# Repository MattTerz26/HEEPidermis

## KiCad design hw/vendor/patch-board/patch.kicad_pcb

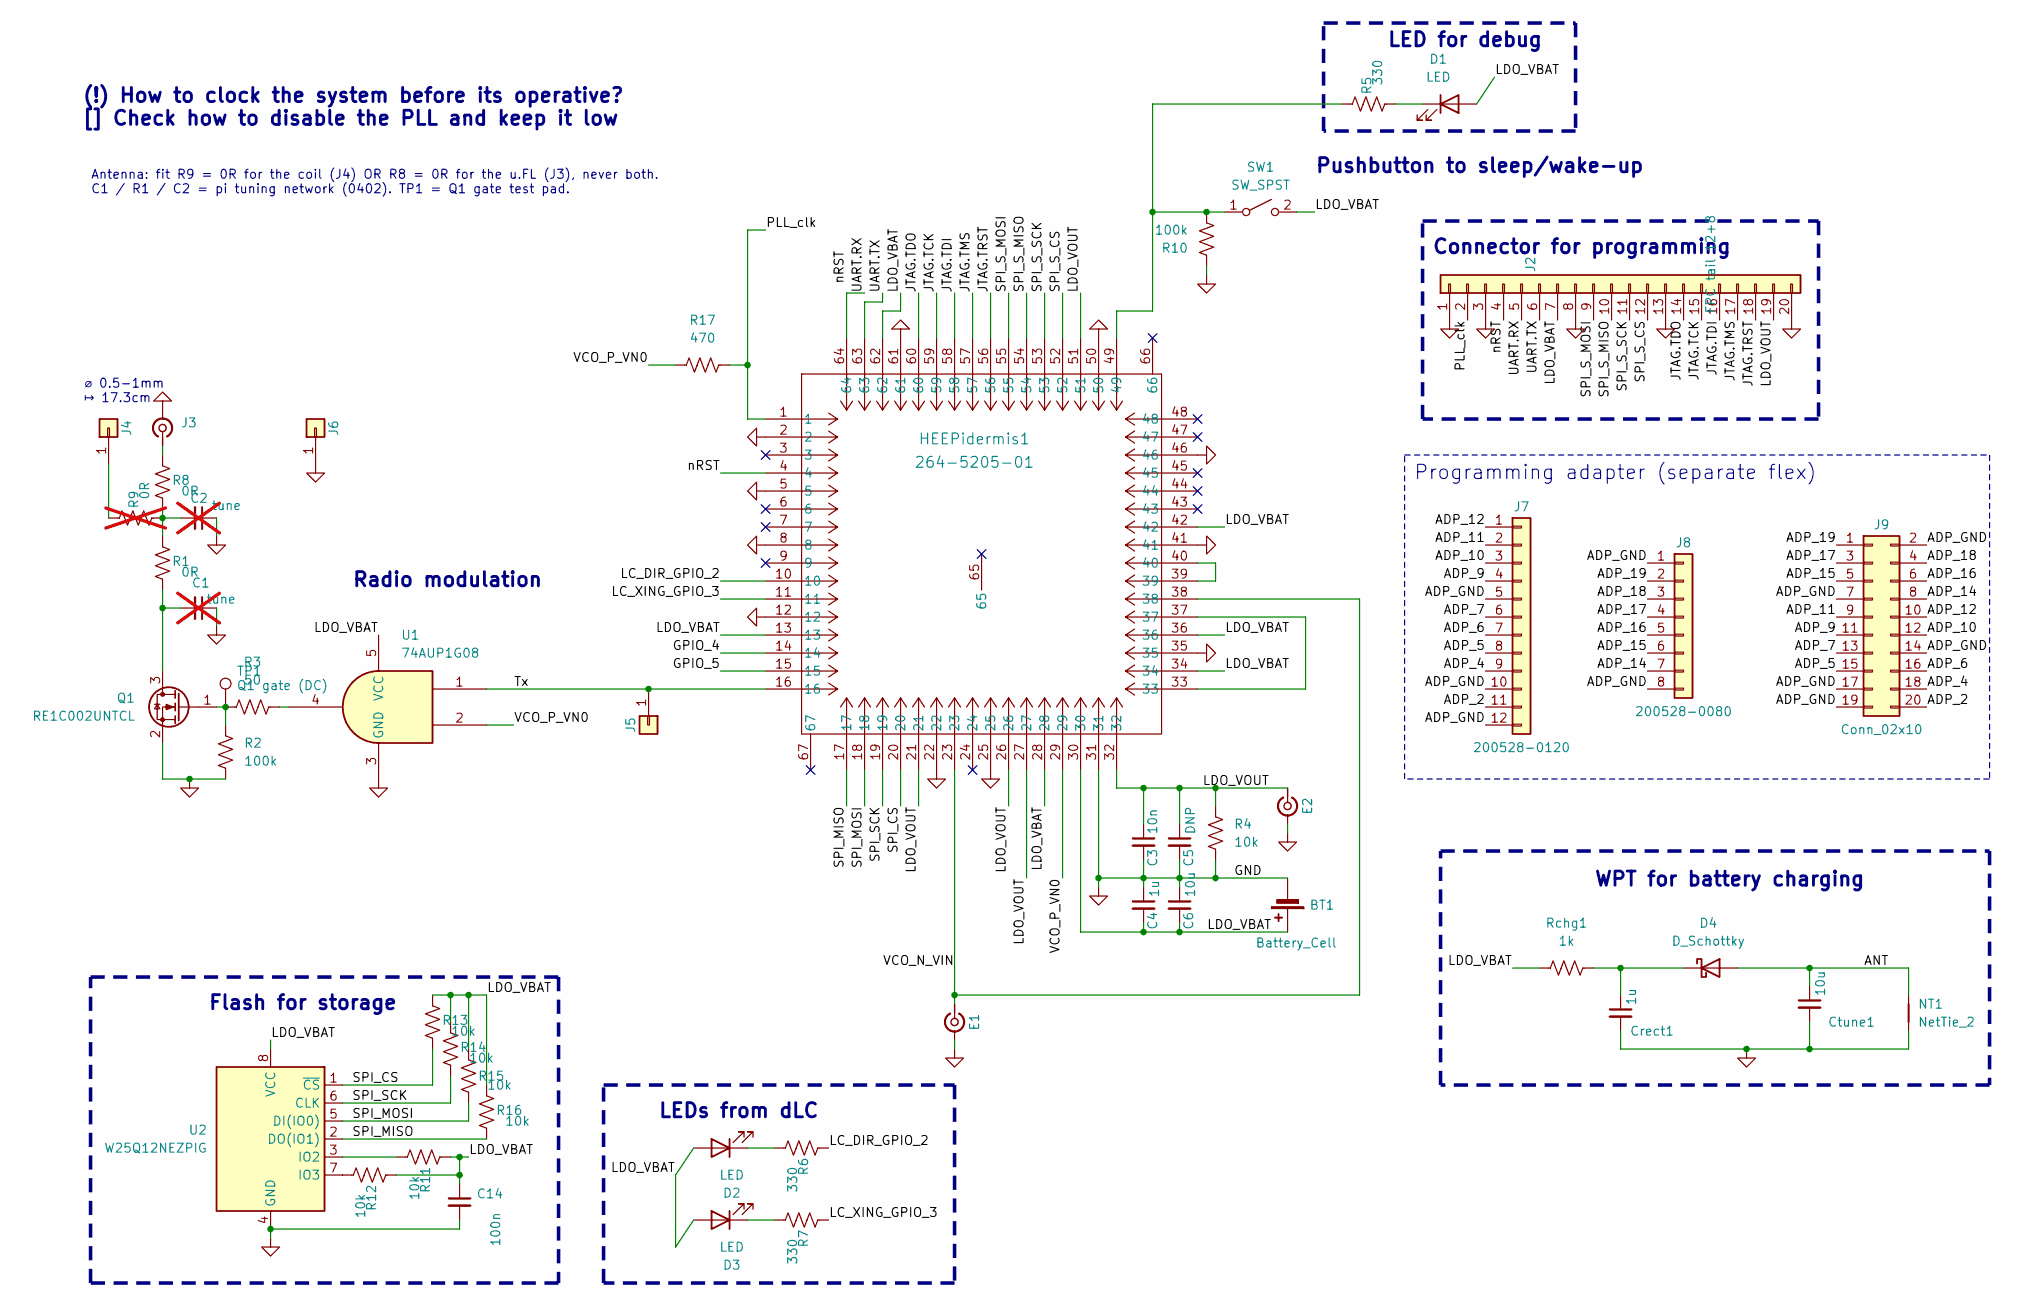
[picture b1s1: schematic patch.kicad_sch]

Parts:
BT1: Battery_Cell; BatteryHolder_Seiko_MS621F
C1, C2: tune; C_0402_1005Metric; not fitted
C3: 10n; C_0603_1608Metric; Mouser Part Number 80-C0805C104Z3V; Digikey Part Number 399-9158-1-ND
C4: 1u; C_0603_1608Metric; Mouser Part Number 80-C0805C104Z3V; Digikey Part Number 399-9158-1-ND
C5: DNP; C_0603_1608Metric; Mouser Part Number 80-C0805C104Z3V; Digikey Part Number 399-9158-1-ND
C6: 10u; C_0603_1608Metric; Mouser Part Number 80-C0805C104Z3V; Digikey Part Number 399-9158-1-ND
C14: 100n; C_0603_1608Metric; Mouser Part Number 80-C0805C104Z3V; Digikey Part Number 399-9158-1-ND
Crect1: 1u; C_0603_1608Metric; Mouser Part Number 80-C0805C104Z3V; Digikey Part Number 399-9158-1-ND
Ctune1: 10u; C_0603_1608Metric; Mouser Part Number 80-C0805C104Z3V; Digikey Part Number 399-9158-1-ND
D1, D2, D3: LED; LED_0603_1608Metric
D4: D_Schottky; D_0603_1608Metric
E1, E2: Conn_Coaxial_Small; 4mm_snap_socket
HEEPidermis1: 264-5205-01; QFN-64-1EP_9x9mm_P0.5mm_EP3.4x3.4mm
J2: FPC tail 12+8; FPC_Tail_2x_P1.00mm_12+8
J3: Conn_Coaxial_Small; U.FL_Molex_MCRF_73412-0110_Vertical
J4, J5, J6: Conn_01x01; PinHeader_1x01_P2.54mm_Vertical
J7: 200528-0120; Molex_200528-0120_1x12-1MP_P1.00mm_Horizontal
J8: 200528-0080; Molex_200528-0080_1x08-1MP_P1.00mm_Horizontal
J9: Conn_02x10; PinHeader_2x10_P2.54mm_Horizontal
NT1: NetTie_2; 1MHz_coil_29x14
Q1: RE1C002UNTCL; SOT-416
R1, R8: 0R; R_0402_1005Metric
R2, R10: 100k; R_0603_1608Metric
R3: 50; R_0603_1608Metric
R4, R11, R12, R13, R14, R15, R16: 10k; R_0603_1608Metric
R5, R6, R7: 330; R_0603_1608Metric
R9: 0R; R_0402_1005Metric; not fitted
R17: 470; R_0603_1608Metric
Rchg1: 1k; R_0603_1608Metric
SW1: SW_SPST; SPST_1.6x3mm
TP1: Q1 gate (DC); TestPoint_Pad_D1.0mm
U1: 74AUP1G08; SOT-353_SC-70-5_Handsoldering
U2: W25Q12NEZPIG; SOIC-8_5.23x5.23mm_P1.27mm

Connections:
/ADP_2: J7.11, J9.20
/ADP_4: J7.9, J9.18
/ADP_5: J7.8, J9.15
/ADP_6: J7.7, J9.16
/ADP_7: J7.6, J9.13
/ADP_9: J7.4, J9.11
/ADP_10: J7.3, J9.12
/ADP_11: J7.2, J9.9
/ADP_12: J7.1, J9.10
/ADP_14: J8.7, J9.8
/ADP_15: J8.6, J9.5
/ADP_16: J8.5, J9.6
/ADP_17: J8.4, J9.3
/ADP_18: J8.3, J9.4
/ADP_19: J8.2, J9.1
/ADP_GND: J7.5, J7.10, J7.12, J8.1, J8.8, J9.2, J9.7, J9.14, J9.17, J9.19
/ANT: Ctune1.1, D4.2 (A), NT1.2
/GPIO_4: HEEPidermis1.14
/GPIO_5: HEEPidermis1.15
/JTAG.TCK: HEEPidermis1.59, J2.15
/JTAG.TDI: HEEPidermis1.58, J2.16
/JTAG.TDO: HEEPidermis1.60, J2.14
/JTAG.TMS: HEEPidermis1.57, J2.17
/JTAG.TRST: HEEPidermis1.56, J2.18
/LC_DIR_GPIO_2: HEEPidermis1.10, R6.2
/LC_XING_GPIO_3: HEEPidermis1.11, R7.2
/LDO_VBAT: BT1.1 (+), C4.2, C6.2, C14.1, D1.2 (A), D2.2 (A), D3.2 (A), HEEPidermis1.13, HEEPidermis1.28, HEEPidermis1.30, HEEPidermis1.34, HEEPidermis1.36, HEEPidermis1.42, HEEPidermis1.62, J2.7, R11.2, R12.2, R13.2, R14.2, R15.2, R16.2, Rchg1.1, SW1.2 (B), U1.5 (VCC), U2.8 (VCC)
/LDO_VOUT: C3.1, C5.1, E2.1 (In_1), HEEPidermis1.21, HEEPidermis1.26, HEEPidermis1.27, HEEPidermis1.32, HEEPidermis1.51, J2.19, R4.1
/PLL_clk: HEEPidermis1.1, J2.2, R17.2
/SPI_CS: HEEPidermis1.20, R13.1, U2.1 (~CS)
/SPI_MISO: HEEPidermis1.17, R16.1, U2.2 (DO(IO1))
/SPI_MOSI: HEEPidermis1.18, R15.1, U2.5 (DI(IO0))
/SPI_SCK: HEEPidermis1.19, R14.1, U2.6 (CLK)
/SPI_S_CS: HEEPidermis1.52, J2.12
/SPI_S_MISO: HEEPidermis1.54, J2.10
/SPI_S_MOSI: HEEPidermis1.55, J2.9
/SPI_S_SCK: HEEPidermis1.53, J2.11
/Tx: HEEPidermis1.16, J5.1 (Pin_1_1), U1.1
/UART.RX: HEEPidermis1.64, J2.5
/UART.TX: HEEPidermis1.63, J2.6
/VCO_N_VIN: E1.1 (In_1), HEEPidermis1.23, HEEPidermis1.38
/VCO_P_VN0: HEEPidermis1.29, R17.1, U1.2
/nRST: HEEPidermis1.4, J2.4
GND: BT1.2 (-), C1.1, C2.1, C3.2, C4.1, C5.2, C6.1, C14.2, Crect1.2, Ctune1.2, E1.2 (Ext), E2.2 (Ext), HEEPidermis1.2, HEEPidermis1.5, HEEPidermis1.8, HEEPidermis1.12, HEEPidermis1.22, HEEPidermis1.25, HEEPidermis1.31, HEEPidermis1.35, HEEPidermis1.41, HEEPidermis1.46, HEEPidermis1.50, HEEPidermis1.61, J2.1, J2.3, J2.8, J2.13, J2.20, J3.2 (Ext), J6.1 (Pin_1_1), NT1.1, Q1.2 (S), R2.1, R4.2, R10.2, U1.3 (GND), U2.4 (GND)
unnamed: C2.2, R1.2, R8.1, R9.1
unnamed: D1.1 (K), R5.1
unnamed: D2.1 (K), R6.1
unnamed: D3.1 (K), R7.1
unnamed: Crect1.1, D4.1 (K), Rchg1.2
unnamed: HEEPidermis1.33, HEEPidermis1.37
unnamed: HEEPidermis1.39, HEEPidermis1.40
unnamed: J3.1 (In), R8.2
unnamed: J4.1 (Pin_1_1), R9.2
unnamed: C1.2, Q1.3 (D), R1.1
unnamed: Q1.1 (G), R2.2, R3.1, TP1.1 (1_1)
unnamed: R3.2, U1.4
unnamed: HEEPidermis1.49, R5.2, R10.1, SW1.1 (A)
unnamed: R11.1, U2.3 (IO2)
unnamed: R12.1, U2.7 (IO3)

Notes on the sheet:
LED for debug
Antenna: fit R9 = 0R for the coil (J4) OR R8 = 0R for the u.FL (J3), never both. C1 / R1 / C2 = pi tuning network (0402). TP1 = Q1 gate test pad.
LEDs from dLC
WPT for battery charging
⌀ 0.5-1mm ↦ 17.3cm
Programming adapter (separate flex)
Flash for storage
(!) How to clock the system before its operative? [] Check how to disable the PLL and keep it low
Connector for programming
Pushbutton to sleep/wake-up
Radio modulation

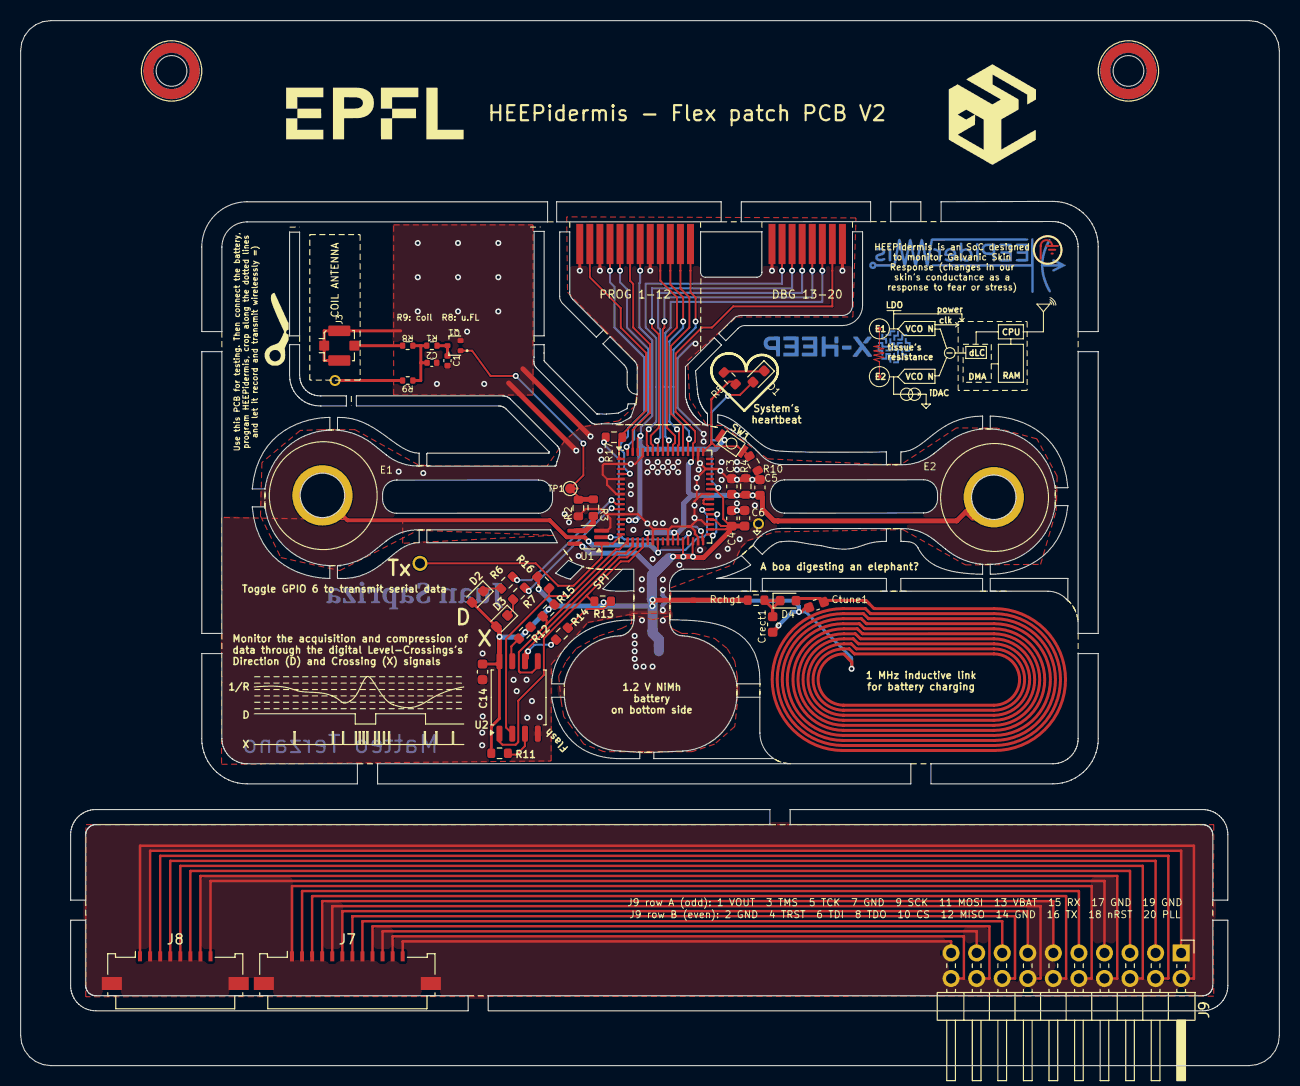
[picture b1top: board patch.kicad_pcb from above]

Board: 2 copper layers, 125.1 x 103.8 mm, 51 parts (1 on the bottom side), 57 nets.

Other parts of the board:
H1, H2: eC 3mm tooling hole; eC_tooling_hole_3mm
